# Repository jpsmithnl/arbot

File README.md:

# arbot
Automatic export from code.google.com/p/arbot failed, so just downloaded and reposted, will convert later

_iRobot Create-Based Robot used for COMP 4766/6778 (Autonomous Robotics), junior enrichment courses, and research on swarm robotics_

  Bio-Inspired Robotics Lab,<br>
  Department of Computer Science,<br>
  Memorial University

= Hardware =

_Released as OSHW under Creative Commons 0 - Public Domain to promote educational and research use._

[arduino_irobot_bridge PCB to interface Arduino and iRobot Create]

= Software =
[iRobot_BlocklyDuino]

[iRobot_Arduino_ROS]

= Contributors =

Created by Jordan Smith and Dr. Andrew Vardy at Memorial University of Newfoundland.

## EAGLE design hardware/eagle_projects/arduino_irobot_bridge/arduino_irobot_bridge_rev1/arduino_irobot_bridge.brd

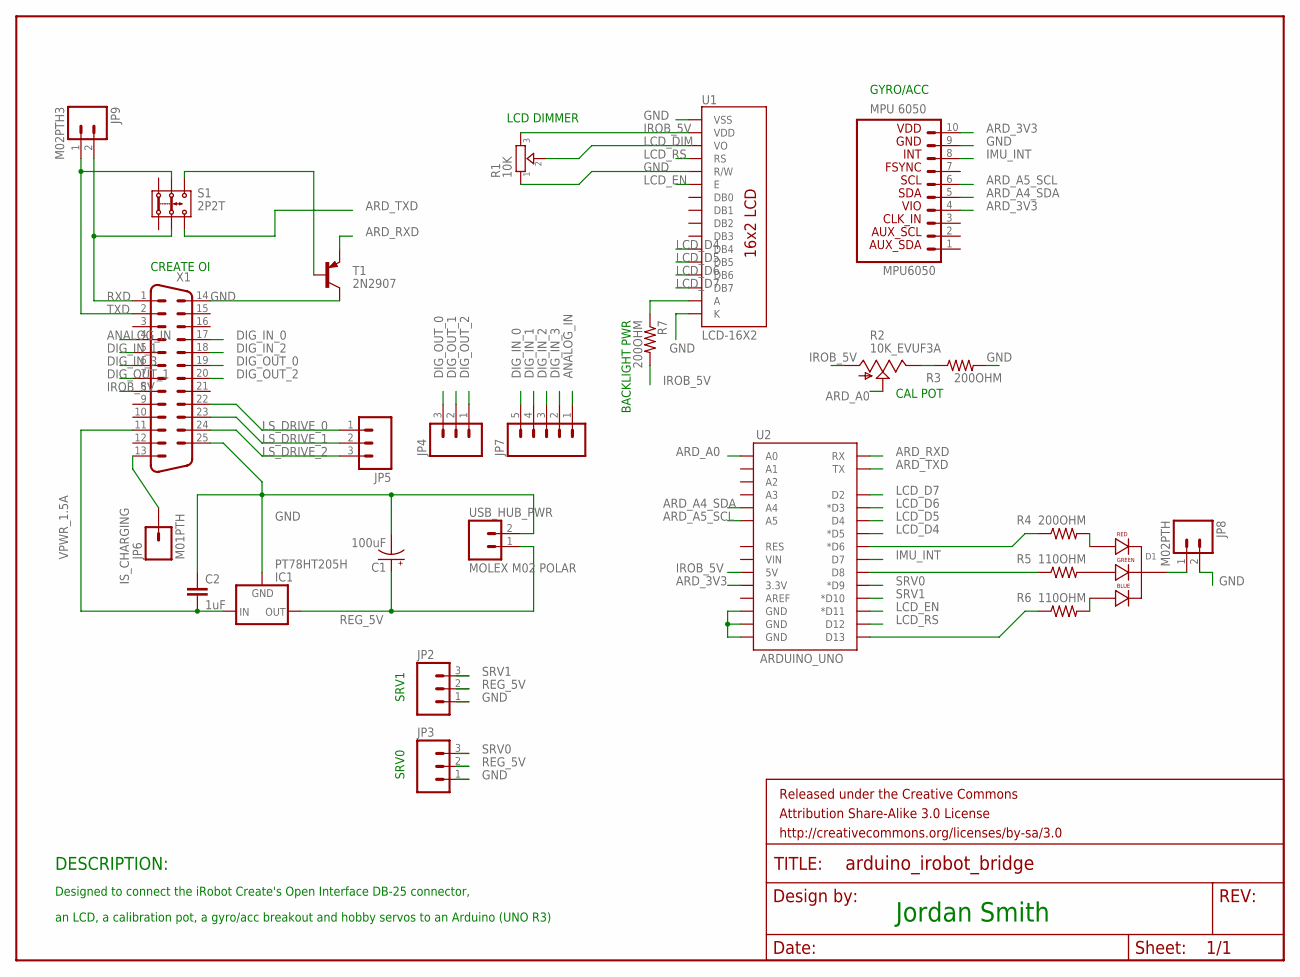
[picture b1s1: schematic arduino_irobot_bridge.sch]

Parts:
C1: 100uF; CPOL-RADIAL-100UF-25V
C2: 1uF; C2.5-2
D1: LED-RGB-CC-THRUCLEAR; LED-RGB-THRU
FRAME1: FRAME-LETTER; CREATIVE_COMMONS
IC1: PT78HT205H; TO220-IGO
JP1: MPU6050; 1X10_LOCK_LONGPADS
JP2, JP3: M03LOCK_LONGPADS; 1X03_LOCK_LONGPADS
JP4, JP5: M03LONGPADS; 1X03_LONGPADS
JP6: M01PTH; 1X01
JP7: M05PTH_LONGPADS; 1X05_LONGPADS
JP8: M02PTH; 1X02
JP9: M02PTH3; 1X02_LONGPADS
R1: 10K; TRIMMER_3306F
R2: 10K_EVUF3A; EVUF
R3, R4, R7: 200OHM; 0207/12
R5, R6: 110OHM; 0207/12
S1: 2P2T
T1: 2N2907; TO92-EBC
U1: LCD-16X2
U2: ARDUINO_UNO; DUEMILANOVE_SHIELD
USB_HUB_PWR: MOLEX M02 POLAR; MOLEX-1X2
X1: DB25VP; M25VP

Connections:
ANALOG_IN: JP7.1, X1.4
ARD_3V3: JP1.4 (VIO), JP1.10 (VDD_3V3), U2.3.3V
ARD_A0: R2.2 (S), U2.A0
ARD_A4_SDA: JP1.5 (SDA), U2.A4
ARD_A5_SCL: JP1.6 (SCL), U2.A5
ARD_RXD: T1.E, U2.RX
ARD_TXD: S1.3.2, U2.TX
DIG_IN_0: JP7.5, X1.17
DIG_IN_1: JP7.4, X1.5
DIG_IN_2: JP7.3, X1.18
DIG_IN_3: JP7.2, X1.6
DIG_OUT_0: JP4.3, X1.19
DIG_OUT_1: JP4.2, X1.7
DIG_OUT_2: JP4.1, X1.20
GND: C1.2 (-), C2.1, IC1.GND, JP1.9 (GND), JP2.1, JP3.1, JP8.2, R1.1, R3.2, T1.C, U1.1 (VSS), U1.5 (R/W), U1.16 (K), U2.GND@0 (GND), U2.GND@1 (GND), U2.GND@2 (GND), USB_HUB_PWR.2, X1.14, X1.25
IMU_INT: JP1.8 (INT), U2.D7
IROB_5V: R1.3, R2.1 (A), R7.2, U1.2 (VDD), U2.5V, X1.8
IS_CHARGING: JP6.1, X1.13
LCD_D4: U1.11 (DB4), U2.D5 (*D5)
LCD_D5: U1.12 (DB5), U2.D4
LCD_D6: U1.13 (DB6), U2.D3 (*D3)
LCD_D7: U1.14 (DB7), U2.D2
LCD_DIM: R1.2, U1.3 (VO)
LCD_EN: U1.6 (E), U2.D11 (*D11)
LCD_RS: U1.4 (RS), U2.D12
LS_DRIVE_0: JP5.1, X1.22
LS_DRIVE_1: JP5.2, X1.23
LS_DRIVE_2: JP5.3, X1.24
unnamed: R7.1, U1.15 (A)
unnamed: R2.3 (E), R3.1
unnamed: D1.1 (RED_CATHODE), R4.2
unnamed: D1.3 (GREEN_CATHODE), R5.2
unnamed: D1.4 (BLUE_CATHODE), R6.2
unnamed: S1.3.1, T1.B
unnamed: D1.2 (CATHODE), JP8.1
unnamed: R4.1, U2.D6 (*D6)
unnamed: R5.1, U2.D8
unnamed: R6.1, U2.D13
REG_5V: C1.1 (+), IC1.OUT, JP2.2, JP3.2, USB_HUB_PWR.1
RXD: JP9.2, S1.2.2, X1.1
SRV0: JP3.3, U2.D9 (*D9)
SRV1: JP2.3, U2.D10 (*D10)
TXD: JP9.1, S1.2.1, X1.2
VPWR_1.5A: C2.2, IC1.IN, X1.11

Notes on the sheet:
Jordan Smith
Designed to connect the iRobot Create's Open Interface DB-25 connector,
an LCD, a calibration pot, a gyro/acc breakout and hobby servos to an Arduino (UNO R3)
DESCRIPTION:
GYRO/ACC
CAL POT
LCD DIMMER
SRV1
SRV0
CREATE OI
BACKLIGHT PWR

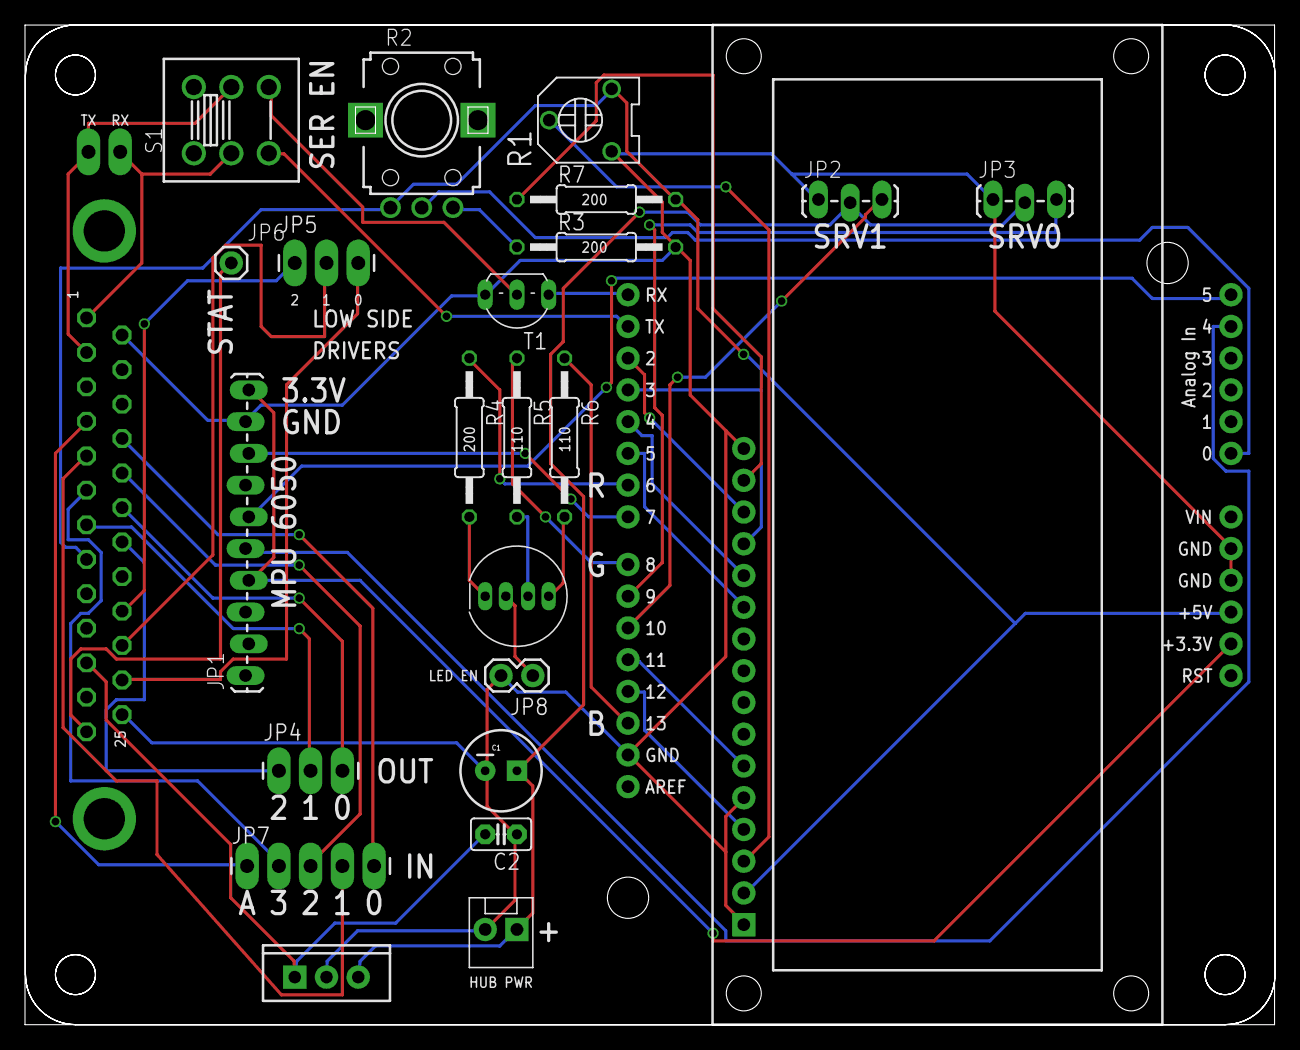
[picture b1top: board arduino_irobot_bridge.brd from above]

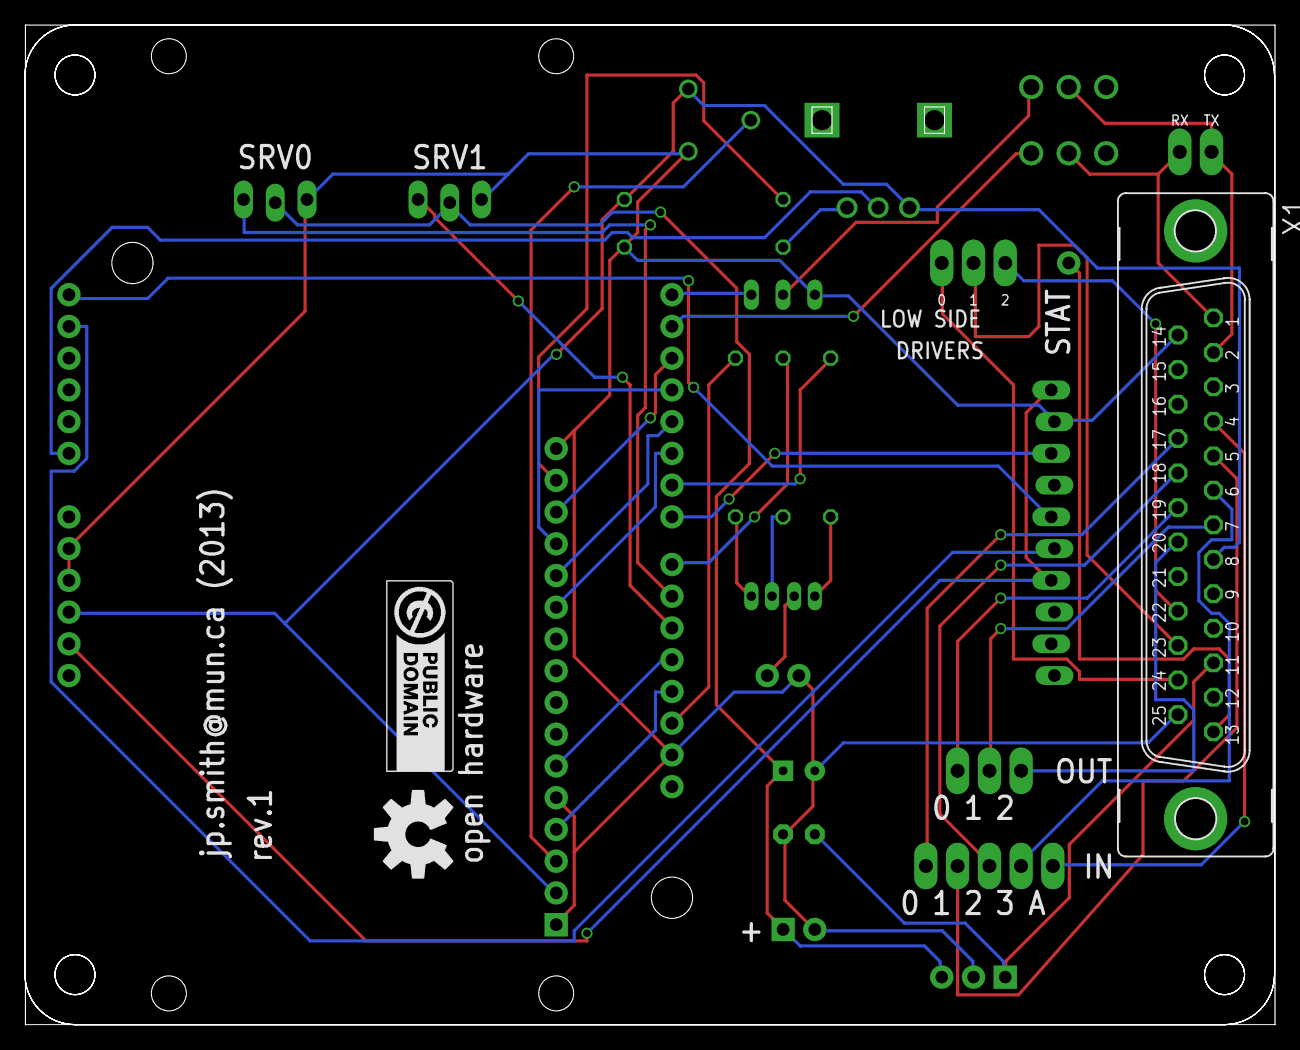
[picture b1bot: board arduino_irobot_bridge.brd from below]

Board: 4 copper layers, 100.0 x 80.0 mm, 32 parts (3 on the bottom side), 44 nets.

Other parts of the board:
U$1, U$2, U$3: DP10080_V1
U$4: OSHW-LOGO-L
U$5: LOGO_CC-0

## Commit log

2015-03-20 committing all the code from Google Code, should convert SVN but since the auto-import tool failed I don't care much for a few old versions
2015-03-20 missed the wiki

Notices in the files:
parts and their libraries:
SparkFun-Connectors: Licensing: CC v3.0 Share-Alike You are welcome to use this library for commercial purposes.
SparkFun-Aesthetics: Released under the Creative Commons Attribution Share-Alike 3.0 License
SparkFun-Aesthetics: http://creativecommons.org/licenses/by-sa/3.0
